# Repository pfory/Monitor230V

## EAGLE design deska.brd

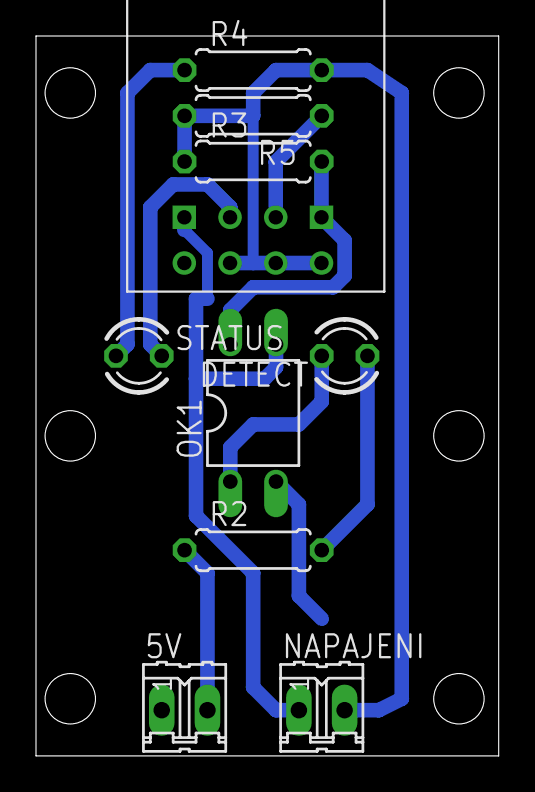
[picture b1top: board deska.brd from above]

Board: 2 copper layers, 25.7 x 40.0 mm, 10 parts (0 on the bottom side), 10 nets.

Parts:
5V: 02P
DETECT: LED3MM
NAPAJENI: 02P
OK1: PC817; DIL04
R2, R5: 1k; 0207/7
R3: 10k; 0207/7
R4: 220; 0207/7
STATUS: LED3MM
U$1: ESP01

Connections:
+3V3: NAPAJENI.2, R3.1, R4.2, R5.2, U$1.CH_PD, U$1.RST, U$1.VCC
GND: NAPAJENI.1, OK1.3, U$1.GND
unnamed: DETECT.A, R2.2
unnamed: DETECT.K, OK1.1
unnamed: 5V.2, R2.1
unnamed: OK1.4, R3.2, U$1.RX
unnamed: 5V.1, OK1.2
unnamed: STATUS.K, U$1.GPIO2
unnamed: R5.1, U$1.GPIO0
unnamed: R4.1, STATUS.A

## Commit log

2018-09-20 init
2018-09-20 blikani led
2018-09-21 + deska
2018-10-02 deska;
2018-10-02 v0.2
2018-10-04 zkraceni intervalu mereni
2018-11-02 v0.3
2019-05-30 - oprava detekce vypadku
2019-08-27 modernizace kodu + ota
2019-08-27 v0,33
